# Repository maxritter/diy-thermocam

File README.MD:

# DIY-Thermocam

The DIY-Thermocam V3 is an open-source thermal imager based on the FLIR Lepton LWIR sensor.

Check out the official website for more information about the project: **[www.diy-thermocam.net](https://www.diy-thermocam.net/)**

**This repository contains:**

- **[Latest firmware releases](https://github.com/maxritter/diy-thermocam/releases)**
- **[Open-source firmware](https://github.com/maxritter/diy-thermocam/tree/master/firmware)**
- **[Desktop software](https://github.com/maxritter/diy-thermocam/tree/master/software)** 
- **[Device enclosure](https://github.com/maxritter/diy-thermocam/tree/master/enclosure)**
- **[Printed circuit board](https://github.com/maxritter/diy-thermocam/tree/master/pcb)**

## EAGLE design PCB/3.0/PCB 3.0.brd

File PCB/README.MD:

# PCB

## General

The printed circuit board has been created with Autosoft Eagle: http://www.autodesk.com/education/free-software/eagle.
Use this software to open the .sch (Schematic) or .brd (Board) files.

You can also use the Gerber.zip and upload it to any PCB service of your choice to manufacture the board, for example http://www.smart-prototyping.com/PCB-Prototyping.html. Dimensions are 89.4mm (w) x 68.4mm (h), 1.6mm thickness and 2 layers.

## Front

## Back

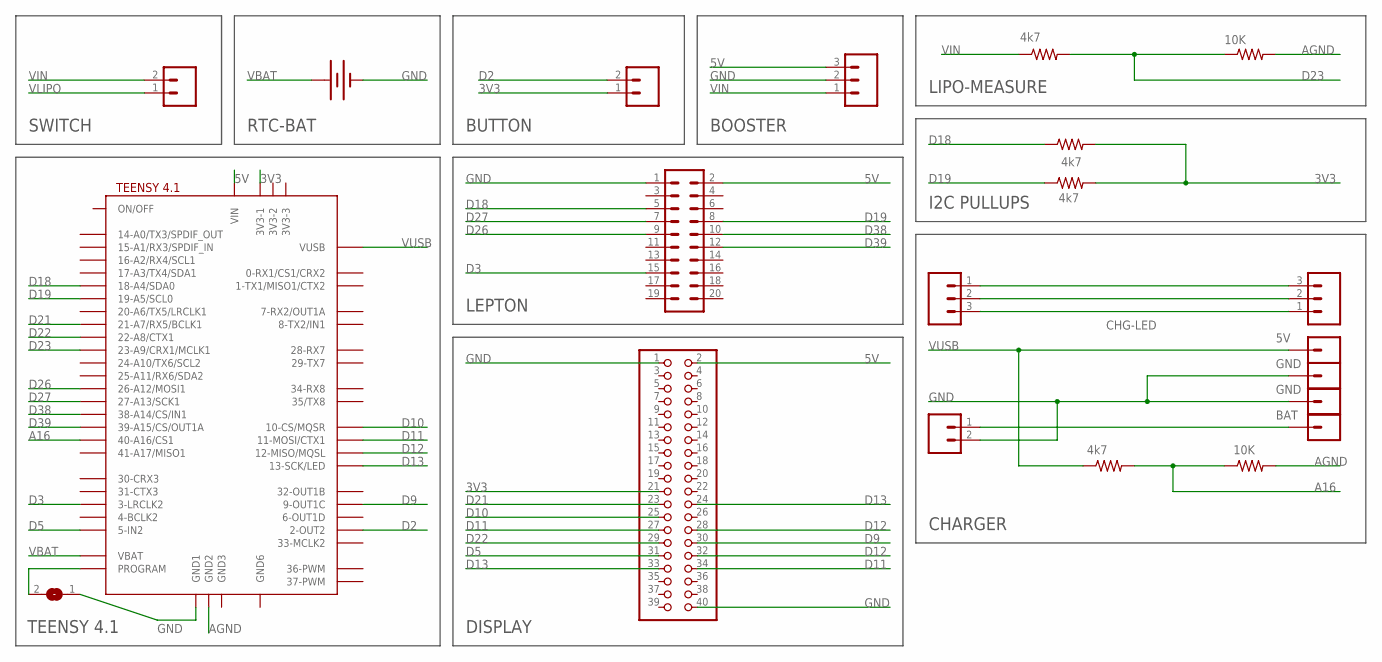
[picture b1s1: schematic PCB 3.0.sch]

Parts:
BAT: BATTERY12PTH; BATTCON_12MM_PTH
BOOSTER: M03PTH; 1X03
BUTTON, BUTTON1: M02PTH; 1X02
CHG-LED: M03PTH; 1X03
J2: CONN_10X2NOSILK; 2X10_NOSILK
JP1, JP2, JP3, JP4: M01PTH; 1X01
LASER1: M03PTH; 1X03
LCD-HEADER: PINHD-2X20; 2X20
PROGRAM: SJ
R1, R3, R4, R6: 4k7; AXIAL-0.4
R2, R5: 10K; AXIAL-0.4
SWITCH: M02PTH; 1X02
U$2: TEENSY41-E; TENNSY41-E

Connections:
3V3: BUTTON.1, LCD-HEADER.21, R4.P$2 (2), R6.P$2 (2), U$2.3V3-1
5V: BOOSTER.3, J2.2, LCD-HEADER.2, U$2.VIN
A16: R3.P$2 (2), R5.P$1 (1), U$2.40-A16/CS1
AGND: R2.P$2 (2), R5.P$2 (2), U$2.GND2
D2: BUTTON.2, U$2.2-OUT2
D3: J2.15, U$2.3-LRCLK2
D5: LCD-HEADER.31, U$2.5-IN2
D9: LCD-HEADER.30, U$2.9-OUT1C
D10: LCD-HEADER.25, U$2.10-CS\MQSR (10-CS/MQSR)
D11: LCD-HEADER.27, LCD-HEADER.34, U$2.11-MOSI/CTX1
D12: LCD-HEADER.28, LCD-HEADER.32, U$2.12-MISO/MQSL
D13: LCD-HEADER.24, LCD-HEADER.33, U$2.13-SCK/LED
D18: J2.5, R4.P$1 (1), U$2.18-A4/SDA0
D19: J2.8, R6.P$1 (1), U$2.19-A5/SCL0
D21: LCD-HEADER.23, U$2.21-A7/RX5/BCLK1
D22: LCD-HEADER.29, U$2.22-A8/CTX1
D23: R1.P$2 (2), R2.P$1 (1), U$2.23-A9/CRX1/MCLK1
D26: J2.9, U$2.26-A12/MOSI1
D27: J2.7, U$2.27-A13/SCK1
D38: J2.10, U$2.38-A14/CS/IN1
D39: J2.12, U$2.39-A15/CS/OUT1A
GND: BAT.GND (-), BOOSTER.2, BUTTON1.2, J2.1, JP1.1, JP2.1, LCD-HEADER.1, LCD-HEADER.40, PROGRAM.1, U$2.GND1
unnamed: CHG-LED.3, LASER1.1
unnamed: CHG-LED.2, LASER1.2
unnamed: CHG-LED.1, LASER1.3
unnamed: PROGRAM.2, U$2.PROGRAM
VBAT: BAT.VCC@1 (+), U$2.VBAT
VIN: BOOSTER.1, R1.P$1 (1), SWITCH.2
VLIPO: BUTTON1.1, JP3.1, SWITCH.1
VUSB: JP4.1, R3.P$1 (1), U$2.VUSB

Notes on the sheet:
CHARGER
DISPLAY
TEENSY 4.1
LEPTON
BUTTON
RTC-BAT
SWITCH
LIPO-MEASURE
BOOSTER
GND
BAT
I2C PULLUPS

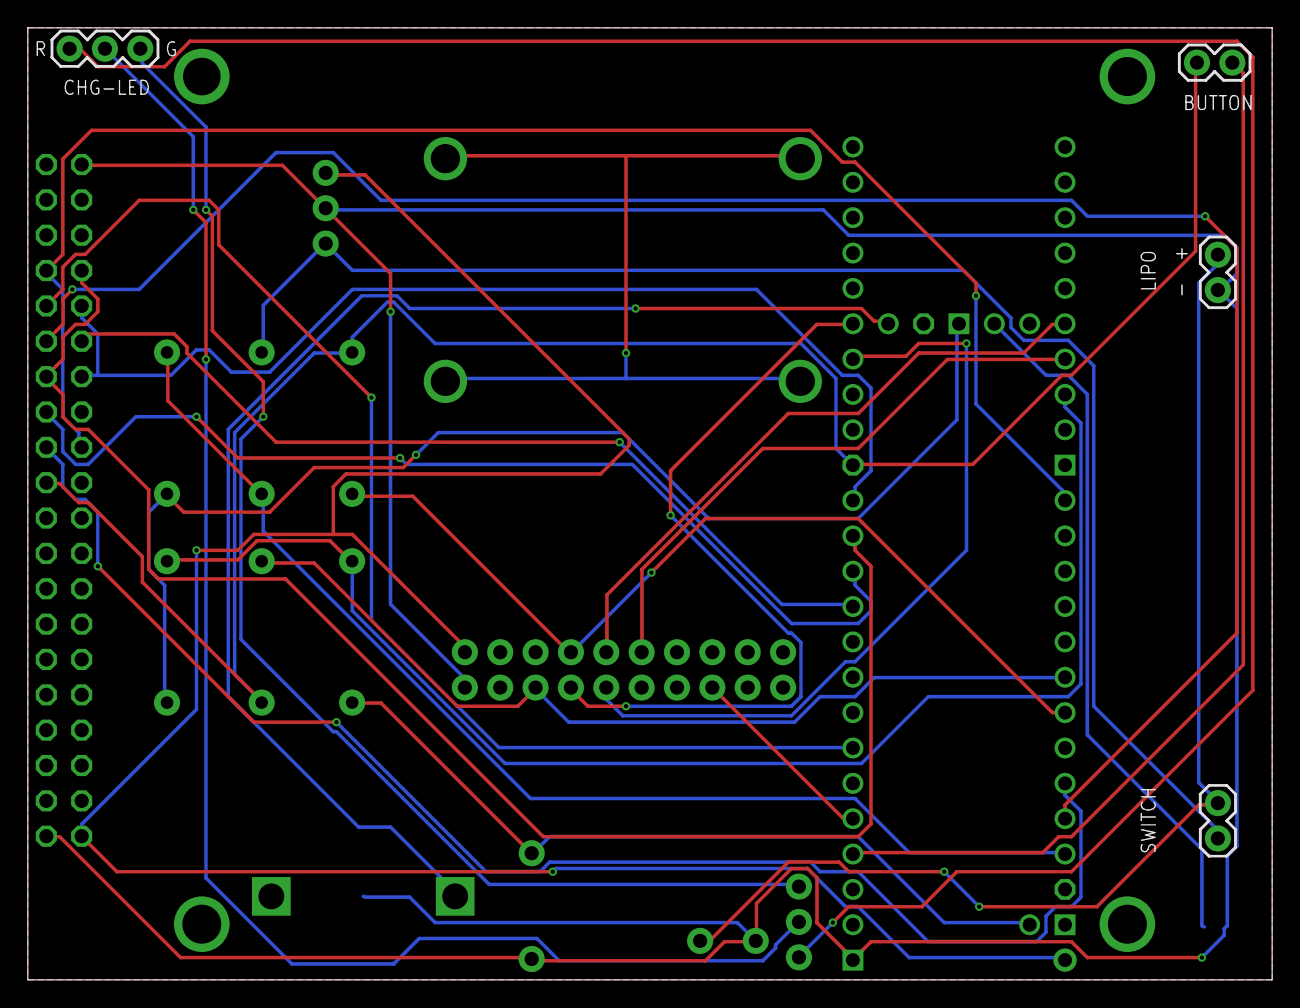
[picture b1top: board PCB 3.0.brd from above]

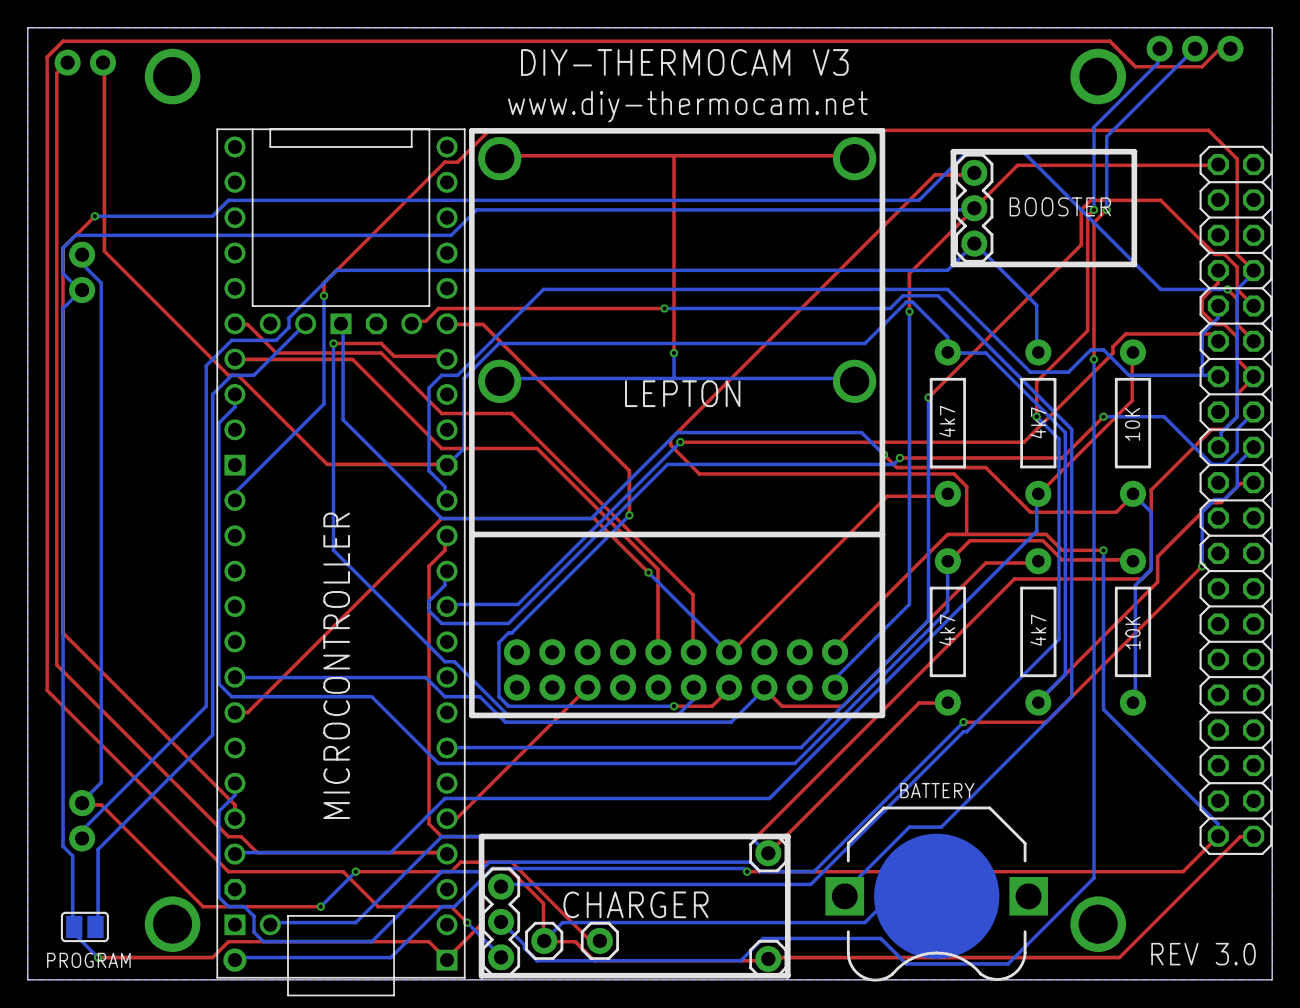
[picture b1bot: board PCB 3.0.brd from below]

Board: 2 copper layers, 89.4 x 68.4 mm, 21 parts (16 on the bottom side), 30 nets.

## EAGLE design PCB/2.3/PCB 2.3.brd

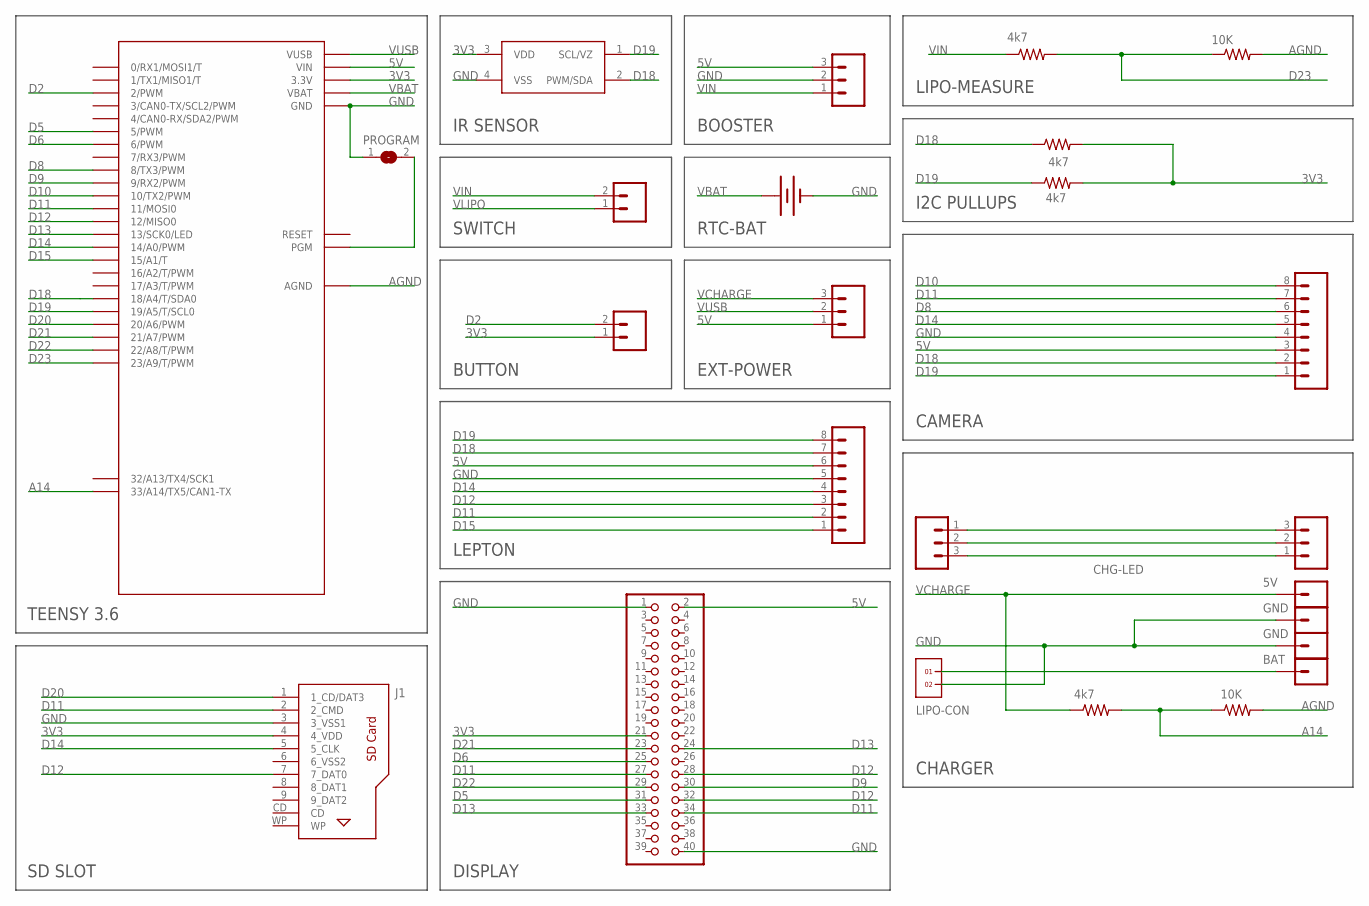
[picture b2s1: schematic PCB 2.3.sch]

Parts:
BAT: BATTERY12PTH; BATTCON_12MM_PTH
BOOSTER: M03PTH; 1X03
BUTTON: M02PTH; 1X02
CHG-LED: M03PTH; 1X03
EXT-POWER: M03PTH; 1X03
J1: 693063020911
JP1, JP2, JP3, JP4: M01PTH; 1X01
LASER1: M03PTH; 1X03
LCD-HEADER: PINHD-2X20; 2X20
LEPTON_MODULE, LEPTON_MODULE1: M08; 1X08_ROUND
LIPO-CON: 1X2
PROGRAM: SJ
R1, R3, R4, R6: 4k7; AXIAL-0.4
R2, R5: 10K; AXIAL-0.4
SWITCH: M02PTH; 1X02
U1: MLX90614_; TO-39
U$1: TEENSY_3.6_ALL_PINS

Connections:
3V3: BUTTON.1, J1.4 (4_VDD), LCD-HEADER.21, R4.P$2 (2), R6.P$2 (2), U1.3 (VDD), U$1.3.3V, U$1.3.3V3 (3.3V), U$1.3.3V4 (3.3V)
5V: BOOSTER.3, EXT-POWER.1, LCD-HEADER.2, LEPTON_MODULE.6, LEPTON_MODULE1.3, U$1.VIN
A14: R3.P$2 (2), R5.P$1 (1), U$1.33/A14 (33/A14/TX5/CAN1-TX)
AGND: R2.P$2 (2), R5.P$2 (2), U$1.AGND
D2: BUTTON.2, U$1.2 (2/PWM)
D5: LCD-HEADER.31, U$1.5 (5/PWM)
D6: LCD-HEADER.25, U$1.6 (6/PWM)
D8: LEPTON_MODULE1.6, U$1.8 (8/TX3/PWM)
D9: LCD-HEADER.30, U$1.9 (9/RX2/PWM)
D10: LEPTON_MODULE1.8, U$1.10 (10/TX2/PWM)
D11: J1.2 (2_CMD), LCD-HEADER.27, LCD-HEADER.34, LEPTON_MODULE.2, LEPTON_MODULE1.7, U$1.11 (11/MOSI0)
D12: J1.7 (7_DAT0), LCD-HEADER.28, LCD-HEADER.32, LEPTON_MODULE.3, U$1.12 (12/MISO0)
D13: LCD-HEADER.24, LCD-HEADER.33, U$1.13 (13/SCK0/LED)
D14: J1.5 (5_CLK), LEPTON_MODULE.4, LEPTON_MODULE1.5, U$1.14/A0 (14/A0/PWM)
D15: LEPTON_MODULE.1, U$1.15/A1 (15/A1/T)
D18: LEPTON_MODULE.7, LEPTON_MODULE1.2, R4.P$1 (1), U1.2 (PWM/SDA), U$1.18/A4 (18/A4/T/SDA0)
D19: LEPTON_MODULE.8, LEPTON_MODULE1.1, R6.P$1 (1), U1.1 (SCL/VZ), U$1.19/A5 (19/A5/T/SCL0)
D20: J1.1 (1_CD/DAT3), U$1.20/A6 (20/A6/PWM)
D21: LCD-HEADER.23, U$1.21/A7 (21/A7/PWM)
D22: LCD-HEADER.29, U$1.22/A8 (22/A8/T/PWM)
D23: R1.P$2 (2), R2.P$1 (1), U$1.23/A9 (23/A9/T/PWM)
GND: BAT.GND (-), BOOSTER.2, J1.3 (3_VSS1), JP1.1, JP2.1, LCD-HEADER.1, LCD-HEADER.40, LEPTON_MODULE.5, LEPTON_MODULE1.4, LIPO-CON.2, PROGRAM.1, U1.4 (VSS), U$1.GND, U$1.GND1 (GND), U$1.GND6 (GND)
unnamed: CHG-LED.3, LASER1.1
unnamed: CHG-LED.2, LASER1.2
unnamed: CHG-LED.1, LASER1.3
unnamed: PROGRAM.2, U$1.PGM
VBAT: BAT.VCC@1 (+), U$1.VBAT
VCHARGE: EXT-POWER.3, JP4.1, R3.P$1 (1)
VIN: BOOSTER.1, R1.P$1 (1), SWITCH.2
VLIPO: JP3.1, LIPO-CON.1, SWITCH.1
VUSB: EXT-POWER.2, U$1.VUSB

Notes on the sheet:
CHARGER
DISPLAY
TEENSY 3.6
CAMERA
LEPTON
IR SENSOR
BUTTON
RTC-BAT
SWITCH
LIPO-MEASURE
BOOSTER
EXT-POWER
GND
BAT
SD SLOT
I2C PULLUPS

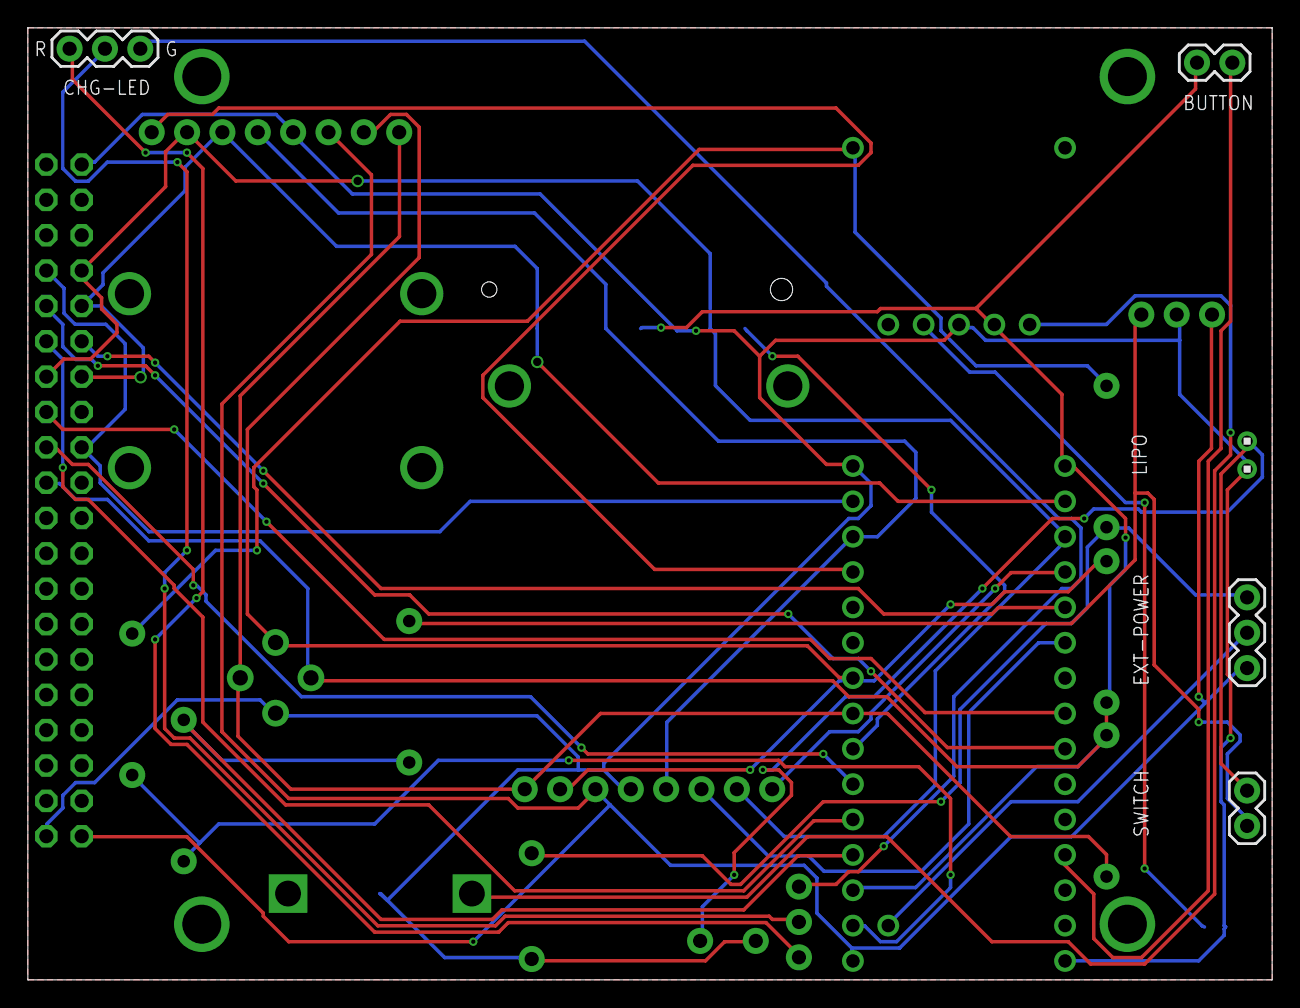
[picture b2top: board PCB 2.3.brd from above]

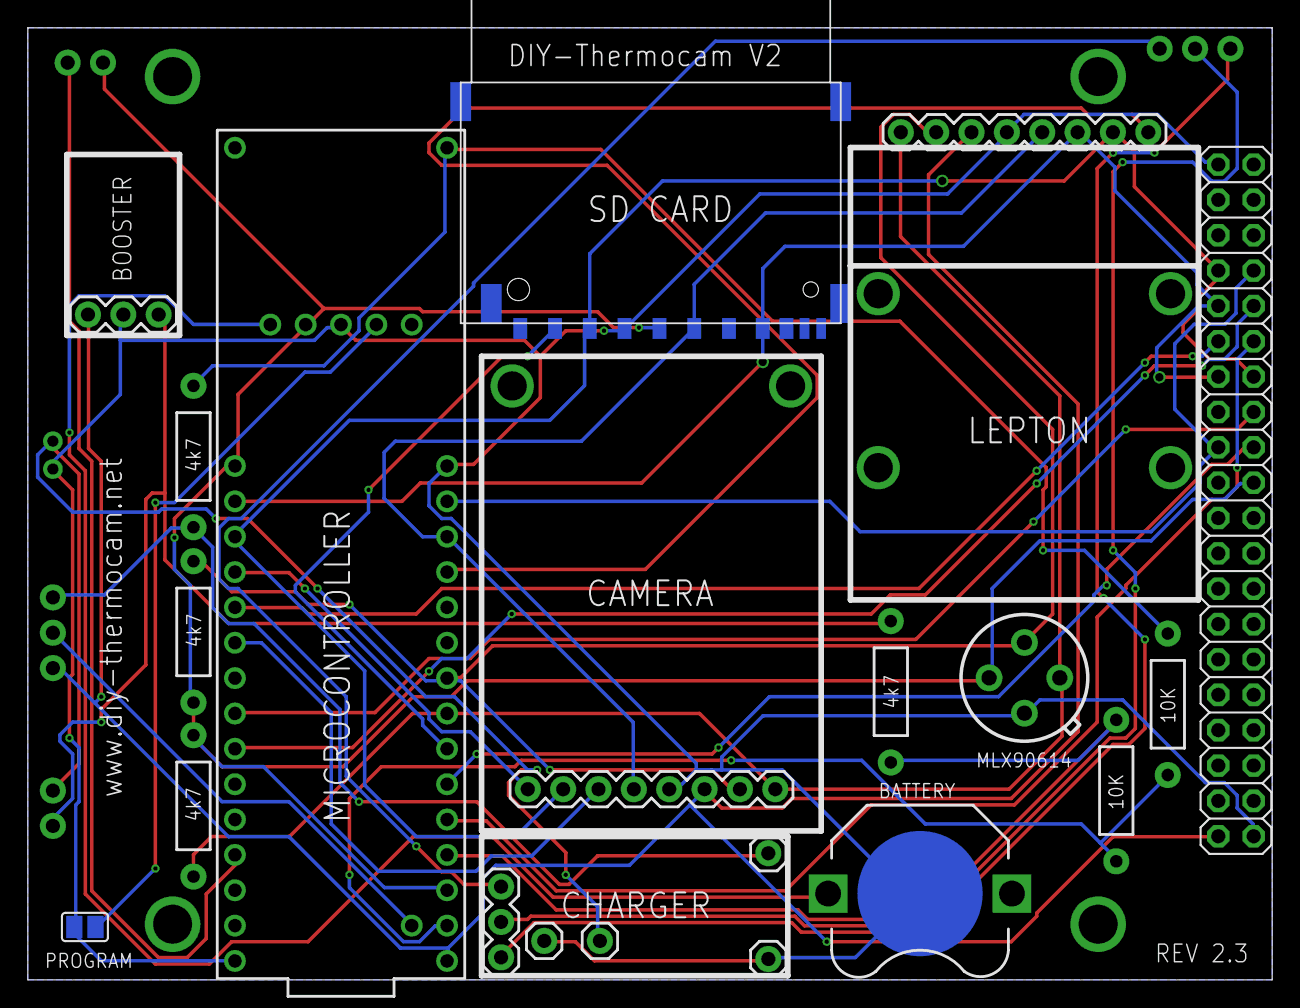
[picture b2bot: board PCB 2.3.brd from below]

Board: 2 copper layers, 89.4 x 68.4 mm, 25 parts (19 on the bottom side), 31 nets.

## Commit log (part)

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2021-06-26 Inner.png: added
2021-06-26 index.md: updated image in sections
2021-06-26 Inner_Trans.png: added
2021-06-26 index.md: updated content in sections
2021-06-26 index.md: changed
2021-06-26 thermal-images.md: updated content in sections
2021-06-26 index.md: updated title in seo
2021-06-26 index.md: updated description in seo
2021-06-26 index.md: updated value in extra
2021-06-26 build-your-own.md: updated markdown_content
2021-06-27 manual.md: added. docs.yml: added page src/pages/docs/manual.md
2021-06-27 manual.md: changed
2021-06-27 manual.md: added
2021-06-27 manual.md: removed
2021-06-27 index.md: added
2021-06-27 usb-protocol.md: removed
2021-06-27 manual: removed
2021-06-27 site-metadata.json: updated nav_links in header
2021-06-27 site-metadata.json: updated style in nav_links
2021-06-27 site-metadata.json: updated label in nav_links
2021-06-27 site-metadata.json: updated url in nav_links
2021-06-27 site-metadata.json: updated new_window in nav_links
2021-06-27 1623780727142.jpg: added
2021-06-27 thermocam.jpg: added
2021-06-27 index.md: updated markdown_content
2021-06-27 docs.jpg: added
2021-06-27 Schematic.JPG: added
2021-06-29 Latest FW changes, still WIP
2021-06-30 Latest changes to V3 firmware - still WIP
2021-07-05 Latest changes to V3 firmware
2021-07-05 index.md: updated label in actions
2021-07-05 index.md: updated url in actions
2021-07-17 Update Teensyduino link
2021-08-04 Refresh page
2021-08-04 stackbit.yaml: Update stackbit.yaml
2021-08-20 Updating Firmware Updater Guide
2021-11-25 building-instructions.md: added. page.yml: added page src/pages/building-instructions.md
2021-11-25 building-instructions.md: added
2021-11-25 building-instructions.md: updated subtitle
2021-11-25 building-instructions.md: updated markdown_content
2021-11-25 build-your-own.md: removed. page.yml: removed page src/pages/build-your-own.md
2021-11-25 building-instructions.md: updated title
2021-11-25 software.md: updated title
2021-11-25 site-metadata.json: updated content in footer
2021-11-25 site-metadata.json: updated links in footer
2021-11-25 index.md: updated sections
2022-10-15 Added Python Source Code for Thermal Live Viewer
2023-04-28 Updated Website
2023-04-28 Fixed images
2023-04-28 Fixed SEO image
2023-04-28 Small changes
2023-05-06 Restructured Repository and General Updates
2023-05-06 Latest updates to website
2023-05-06 Bugfixes
2023-05-06 Latest changes
2023-05-07 Updated Device Firmware to 3.0.3
2023-05-07 Updated instructions for firmware flashing
2023-05-07 Small changes to index
2023-05-07 Small changes to site
2023-05-07 Updated partlist
2023-05-07 Updated Building Instructions
2023-10-20 Added support for FLIR Lepton3.1R
2024-10-23 Remove GroupGets Kit
2024-10-23 Remove year
2024-10-23 Change Title
2024-10-23 Update title
2025-02-17 Made changes to live_viewer.py and main.py SAve Video
2025-02-17 cleanup
2025-02-17 added the module in requirements list
2025-02-17 import cv2
2025-02-23 Added Comport Selection Menu and fixed a bug
2025-11-08 Added tracking

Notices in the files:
parts and their libraries:
SparkFun-Connectors: Licensing: Creative Commons ShareAlike 4.0 International - https://creativecommons.org/licenses/by-sa/4.0
EAGLE-INPUT_OUTPUT_CONNECTORS-rev16b: Copyright: Würth Elektronik
